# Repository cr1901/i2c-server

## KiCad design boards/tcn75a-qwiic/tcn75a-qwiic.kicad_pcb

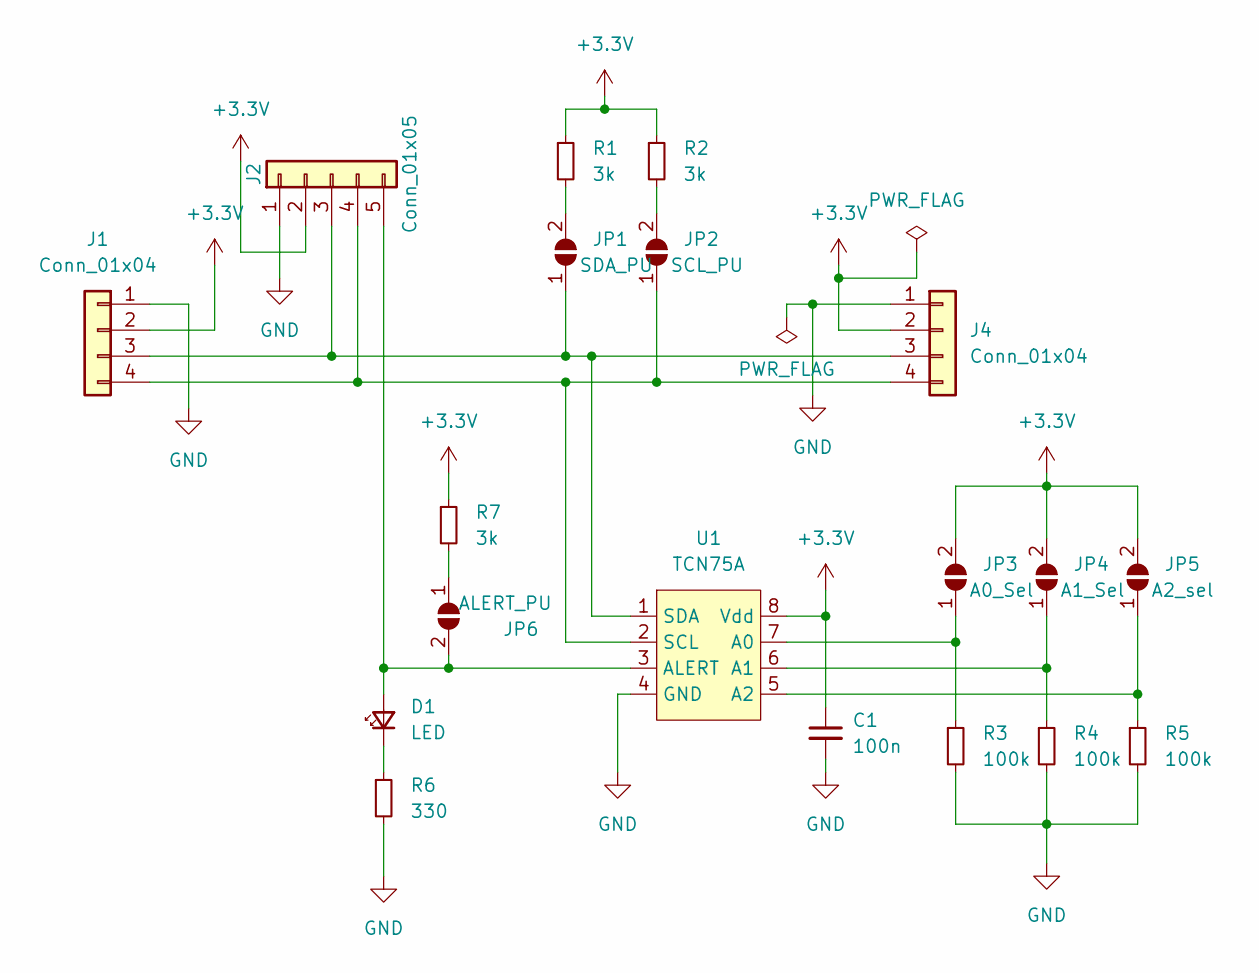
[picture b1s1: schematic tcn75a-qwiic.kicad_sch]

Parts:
C1: 100n; C_0603_1608Metric
D1: LED; LED_0603_1608Metric
J1, J4: Conn_01x04; JST_SH_SM04B-SRSS-TB_1x04-1MP_P1.00mm_Horizontal
J2: Conn_01x05; PinHeader_1x05_P2.54mm_Vertical
JP1: SDA_PU; SolderJumper-2_P1.3mm_Open_RoundedPad1.0x1.5mm
JP2: SCL_PU; SolderJumper-2_P1.3mm_Open_RoundedPad1.0x1.5mm
JP3: A0_Sel; SolderJumper-2_P1.3mm_Open_RoundedPad1.0x1.5mm
JP4: A1_Sel; SolderJumper-2_P1.3mm_Open_RoundedPad1.0x1.5mm
JP5: A2_sel; SolderJumper-2_P1.3mm_Open_RoundedPad1.0x1.5mm
JP6: ALERT_PU; SolderJumper-2_P1.3mm_Open_RoundedPad1.0x1.5mm
R1, R2, R7: 3k; R_0603_1608Metric
R3, R4, R5: 100k; R_0603_1608Metric
R6: 330; R_0603_1608Metric
U1: TCN75A; MSOP-8_3x3mm_P0.65mm

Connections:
+3.3V: C1.1, J1.2, J2.2, J4.2, JP3.2 (B), JP4.2 (B), JP5.2 (B), R1.1, R2.1, R7.1, U1.8 (Vdd)
GND: C1.2, J1.1, J2.1, J4.1, R3.2, R4.2, R5.2, R6.2, U1.4 (GND)
unnamed: D1.1 (K), R6.1
unnamed: J1.3, J2.3, J4.3, JP1.1 (A), U1.1 (SDA)
unnamed: J1.4, J2.4, J4.4, JP2.1 (A), U1.2 (SCL)
unnamed: JP1.2 (B), R1.2
unnamed: JP2.2 (B), R2.2
unnamed: JP6.1 (A), R7.2
unnamed: D1.2 (A), J2.5, JP6.2 (B), U1.3 (ALERT)
unnamed: JP5.1 (A), R5.1, U1.5 (A2)
unnamed: JP4.1 (A), R4.1, U1.6 (A1)
unnamed: JP3.1 (A), R3.1, U1.7 (A0)

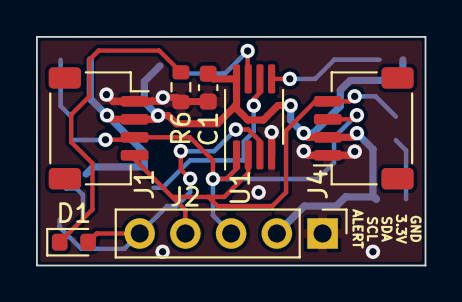
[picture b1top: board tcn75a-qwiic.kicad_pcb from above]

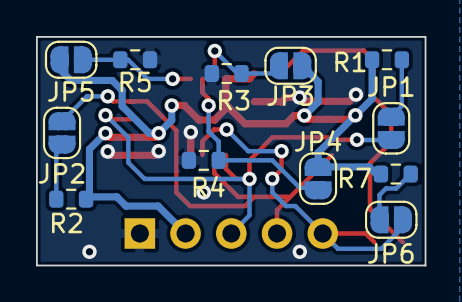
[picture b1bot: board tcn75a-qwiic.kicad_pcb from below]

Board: 2 copper layers, 21.6 x 12.7 mm, 19 parts (12 on the bottom side), 12 nets.

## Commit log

2020-07-14 Initial commit.
2020-07-14 Set temp reading to 12 bits in init. Add CSV format output.
2020-07-15 Convert into workspace, make sure code compiles on Windows.
2020-07-15 Add .gitignore.
2020-07-15 Create skeleton of http server and i2c read loop.
2020-07-16 Get working code on Linux, implement Mutex for data sharing.
2020-07-16 Send temp data over socket.
2020-07-18 Implement server sending with base64.
2020-07-18 Use hyper crate to implement http server.
2020-07-18 Make sure server runs on Linux.
2020-07-18 Cleanup unused imports and warnings.
2020-07-19 Add SampleBuf wrapper struct.
2020-07-19 Add Serialization support to SampleBuf.
2020-07-19 Create arguments parser.
2020-07-19 Thread arguments to rest of program.
2020-07-19 Attempt to slim down output server.
2020-07-19 cargo fmt. Add missing Sealed impls.
2020-07-20 Improve replay_synthesize function for debugging purposes.
2020-07-20 Add stopgap Python plotter for now.
2020-07-20 Fix from_raw_parts oversight in byte_data len.
2020-07-20 b64decode needs to use URL-safe variant of base64.
2020-07-22 Fix another sizeof oversight in Serialize impl.
2020-07-23 Remove unwraps that don't come from clap matches.
2020-08-05 Turn compress into library crate.
2020-08-06 Checkpoint commit.
2020-08-06 Attempt an implementation of the wire protocol
2020-08-06 Fix encoder to match spec.
2020-08-06 Move spec to top of file, add more tests (decode fails).
2020-08-07 Fix decode routine.
2020-08-07 Add tcn75a crate to workspace (not started).
2020-08-07 Deliberately add line of whitespace before inner attributes in compress so Atom doesn't treat the file as always out-of-date.
2020-08-07 Start adding some docs for compression.
2020-09-18 Start constructing tcn75a crate.
2020-09-18 Use macros to implement ORing config register fields together.
2020-09-21 Add mock i2c object for testing temp sensor.
2020-09-21 Suppress unused var and dead code warnings for now.
2020-09-21 Cache register pointer to avoid repeated writes.
2020-09-22 Make set_reg_ptr public, panic on invalid input.
2020-09-22 More reg_ptr tests.
2020-09-22 Fill out Tcn75aError enum.
2020-09-22 Use RegPtrError variant.
2020-09-22 Start adding docs to tcn75a.
2020-09-23 Improve doc links.
2020-09-23 Add documentation for set_reg_ptr and free methods.
2020-09-23 Create stubs for remaining API functions.
2020-09-29 Use stable version of embedded-hal for now.
2020-09-29 Start adding doctests (mostly for Linux for now).
2020-09-29 Make sure doctests compile on Linux and not Linux.
2020-09-29 Add second example doctest.
2020-09-30 Make config reg types public.
2020-09-30 Add minimal integration tests to tcn75a.
2020-09-30 Implement setting limits part of API for tcn75a.
2020-09-30 tcn75a: Add unit tests for Limits.
2020-09-30 tcn75a: Add docs for limit module, impl Clone/Copy for Limits.
2020-10-01 tcn75a: Document config reg enums.
2020-10-01 tcn75a: Rewrite ConfigReg type- use bitfield proc macro.
2020-10-01 tcn75a: Clean up already-implemented API functions.
2020-10-01 tcn75a: Documentation improvements.
2020-10-01 tcn75a: cargo fmt.
2020-10-01 tcn75a: Fix I2C write-reads which were not handled properly.
2020-10-01 tcn75a: Remove WriteRead trait bound. Due to caching, we don't use it.
2020-10-01 tcn75a: Implement set/get config register.
2020-10-01 tcn75a: Implement caching of config register contents.
2020-10-01 tcn75a: Create remaining test vectors (unimplemented tests).
2020-10-02 tcn75a: Add some missing temperature register test implementations. Fix bug in temperature() found by tests.
2020-10-03 tcn75a: Add remaining unit tests, update some comments.
2020-10-03 tcn75a: use Error type alias in all functions.
2020-10-03 tcn75a: Add docs to temperature/config_reg.
2020-10-03 tcn75a: Add example to free method.
2020-10-03 tcn75a: Add docs for set_config_reg, modify config_reg example.
2020-10-04 tcn75a: Stopgap commit adding more documentation.
2020-10-04 tcn75a: Fix caching behavior for set_config_reg.
2020-10-04 tcn75a: Fix caching behavior for set_limits. Minor doc tweaks.
2020-10-04 tcn75a: Add remaining documentation and examples.
2020-10-04 tcn75a: Flesh out integration test a bit (will be improved later).
2020-10-04 tcn75a: Add README.md.
2020-10-05 Update README.md. Add CHANGELOG.md.
2020-10-06 tcn75a: Make cfg_if usage more visually pleasing in Atom.
2020-10-06 tcn75a: Add plotting/data capture example.
2020-10-07 tcn75a: Remove impl_field macro and impl config enums directly.
2020-10-07 tcn75a: Implement From/TryFrom for Resolution and FaultQueue.
2020-10-07 tcn75a: Improve plot example with new conversions.
2021-03-15 tcn75a: Minor documentation updates.
2021-03-15 tcn75a: Add limits example (to be expanded).
2021-03-15 tcn75a: Start introducting fixed point representation for temperature and limits. Tests fail, examples work.
2021-03-15 tcn75a: Fix failing tests from introducing fixed point.
2021-03-15 tcn75a: Change create_read_free test to make fixed point representation more explicit.
2021-03-16 tcn75a: Scale back implemented traits for Temperature.
2021-03-19 tcn75a: Introduce fixed_macro, convert Limits struct to use I8F8 representation. Tests pass, documentation out of date.
2021-03-19 tcn75a: Bring set_limits docs up to date (discuss invariants).
2021-03-19 tcn75a: Give Temperature struct documentation, remove Default trait (not needed anymore).
2021-03-19 tcn75a: Bring limits docs up to date.
2021-03-19 tcn75a: Update modular-bitfield and crossterm dependencies.
2021-03-19 tcn75a: Move crossterm to linux-only deps for now.
2021-03-19 tcn75a: cargo fmt (plus my minor changes).
2021-03-19 tcn75a: Fix unused import warnings.
2021-03-24 compress: Fix bitvec dependency to point to tag instead of branch (for now).
2021-03-25 tcn75a: Implement Display for error types and use eyre for limits example.
2021-03-25 tcn75a: Reimplement Tcn75aError closer to intended. Also cargo fmt.
2021-03-25 tcn75a: Remove most derived traits from Temperature- convert to I8F8 to use.
2021-03-25 tcn75a: Add ConfigRegValueError unit test.
2021-03-25 tcn75a: Correct out-of-date documentation.
2021-03-25 tcn75a: Add missing LICENSE files.
2021-03-25 tcn75a: More documentation fixes.
2021-03-29 Start reworking the compression algorithm to be more efficient.
2021-03-29 More compression algorithm tweaking.
2021-03-29 Finish reworking compression docs for now.
2021-03-29 I lied. More tweaks.
2021-03-29 compress: Fix typo in compression table.
2021-03-29 compress: Document why I changed the order of the compression table.
2021-03-29 Attempt to reduce number of bits low zero runs take.
2021-03-29 Move RLE, Events, and Absolute to 4-bit prefix to reclaim 3-bit prefixes for diffs.
2021-03-29 Encode diffs to miminize the number of bits difference between 1 sample and 16 samples.
2021-03-29 compress: Upgrade bitvec to most recent version.
2021-03-30 compress: Fix code so it compiles without needing Cell.
2021-04-05 tcn75a: Fix clippy lints. Cargo fmt.
2021-04-05 tcn75a: Consult Rust API Guidelines Checklist to implement/unimplement common traits.
2021-05-12 tcn75a: Expose values read in Tcn75aError::LimitError.
2021-05-13 plot: Add some more entropy calculations.
2021-05-13 compress: Create a struct to hold RLE state.
2021-06-20 tcn75a: Quality-of-life changes to examples.
2021-06-21 tcn75a: Refactor and simplify implementation of Tcn75aError to be generic over all types.
2021-06-21 tcn75a: Add crate-level example.
2021-06-21 tcn75a: Add missing Cargo.toml metadata.
2021-06-21 tcn75a: Add html_root_url attribute and test that it remains in sync.
2021-06-22 tcn75a: Add badges to README.md. Tag tcn75a-v0.1.0.
2022-01-24 Add raw i16 to OutOfRange error variant for debugging. Bump version to 0.2.
2022-01-24 tcn75a: Bump embedded HAL to 1.0.0 alpha version. NFC.
2022-05-05 tcn75a: Make sure crate compiles with Embedded HAL alpha 8. Not tested beyond compile.
2022-07-14 tcn75a: Bump embedded HAL to 1.0.0-alpha.8 and fix tests. NFC.
2022-07-22 tcn75a: Create iter_mut for iterating over temperature readings.
2023-01-22 Add kicad files for tcn75a QWIIC board.
2024-10-06 Bring tcn75a up to parity with embedded-hal 1.0.
2024-10-06 Fix tests broken up API and crate updates.
2024-10-07 Use iter::repeat_with in place of iter_mut/IterMut, remove from API.
2024-10-07 Update CHANGELOG.md, add test to ensure its updated. Tag tcn75a-v0.2.0.
2024-10-10 Use exponential moving average for plot demo for prettier plots.
